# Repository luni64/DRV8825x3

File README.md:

# DRV8825x3
Carrier for 3 DRV8825 Stepper drivers

[Board and Schematic (pdf)](https://github.com/luni64/DRV8825x3/raw/master/media/)

### See also here https://github.com/luni64/mmStep for a [SparkFun MicroMode](https://www.sparkfun.com/micromod) compatible carrier for 4 DRV8825 boards.

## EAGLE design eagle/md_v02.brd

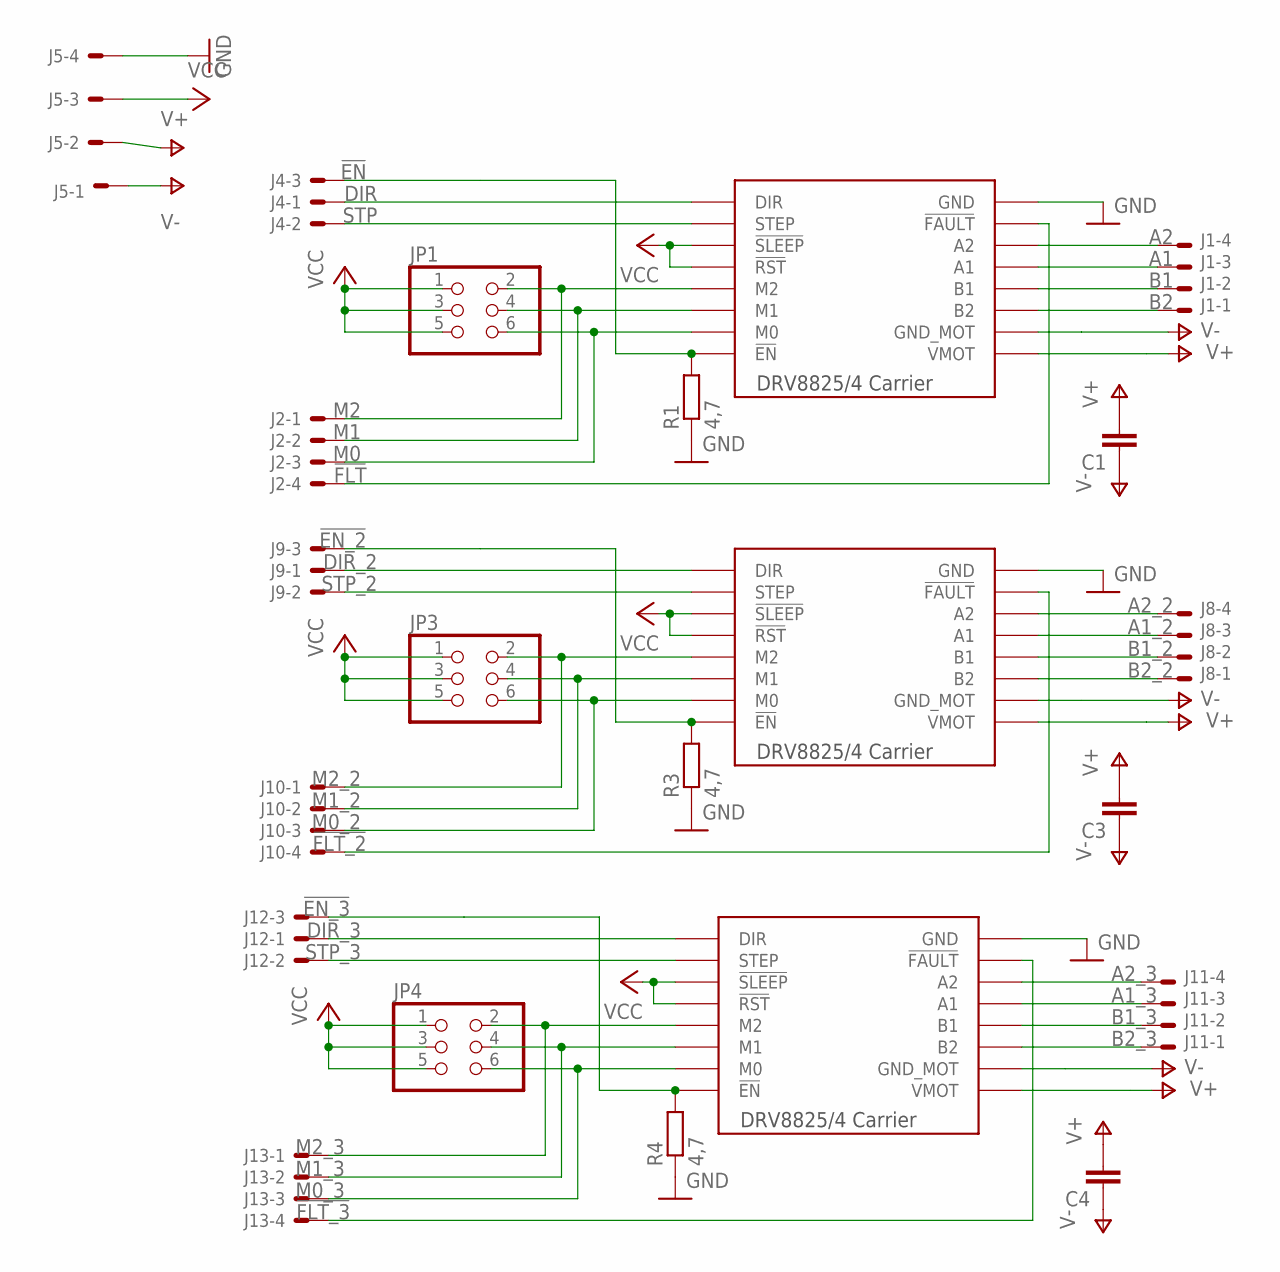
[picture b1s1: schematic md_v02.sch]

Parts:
C1, C3, C4: C-EU050-035X075; C050-035X075
J1, J2, J5, J8, J10, J11, J13: 22-27-2041-04; 6410-04
J4, J9, J12: 22-27-2031-03; 6410-03
JP1, JP3, JP4: PINHD-2X3; 2X03
M1, M3, M4: DRV8825_CARRIER"; DRV882_CARRIER
R1, R3, R4: 4,7; 0204/7

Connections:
!EN: J4.3, M1.EN (!EN), R1.2
!EN_2: J9.3, M3.EN (!EN), R3.2
!EN_3: J12.3, M4.EN (!EN), R4.2
!FLT: J2.4, M1.!FLT (!FAULT)
!FLT_2: J10.4, M3.!FLT (!FAULT)
!FLT_3: J13.4, M4.!FLT (!FAULT)
A1: J1.3, M1.A1
A1_2: J8.3, M3.A1
A1_3: J11.3, M4.A1
A2: J1.4, M1.A2
A2_2: J8.4, M3.A2
A2_3: J11.4, M4.A2
B1: J1.2, M1.B1
B1_2: J8.2, M3.B1
B1_3: J11.2, M4.B1
B2: J1.1, M1.B2
B2_2: J8.1, M3.B2
B2_3: J11.1, M4.B2
DIR: J4.1, M1.DIR
DIR_2: J9.1, M3.DIR
DIR_3: J12.1, M4.DIR
GND: J5.4, M1.GND, M3.GND, M4.GND, R1.1, R3.1, R4.1
M0: J2.3, JP1.6, M1.M0
M0_2: J10.3, JP3.6, M3.M0
M0_3: J13.3, JP4.6, M4.M0
M1: J2.2, JP1.4, M1.M1
M1_2: J10.2, JP3.4, M3.M1
M1_3: J13.2, JP4.4, M4.M1
M2: J2.1, JP1.2, M1.M2
M2_2: J10.1, JP3.2, M3.M2
M2_3: J13.1, JP4.2, M4.M2
STP: J4.2, M1.STEP
STP_2: J9.2, M3.STEP
STP_3: J12.2, M4.STEP
V+: C1.2, C3.2, C4.2, J5.2, M1.VMOT, M3.VMOT, M4.VMOT
V-: C1.1, C3.1, C4.1, J5.1, M1.GND_MOT, M3.GND_MOT, M4.GND_MOT
VCC: J5.3, JP1.1, JP1.3, JP1.5, JP3.1, JP3.3, JP3.5, JP4.1, JP4.3, JP4.5, M1.RST (!RST), M1.SLP (!SLEEP), M3.RST (!RST), M3.SLP (!SLEEP), M4.RST (!RST), M4.SLP (!SLEEP)

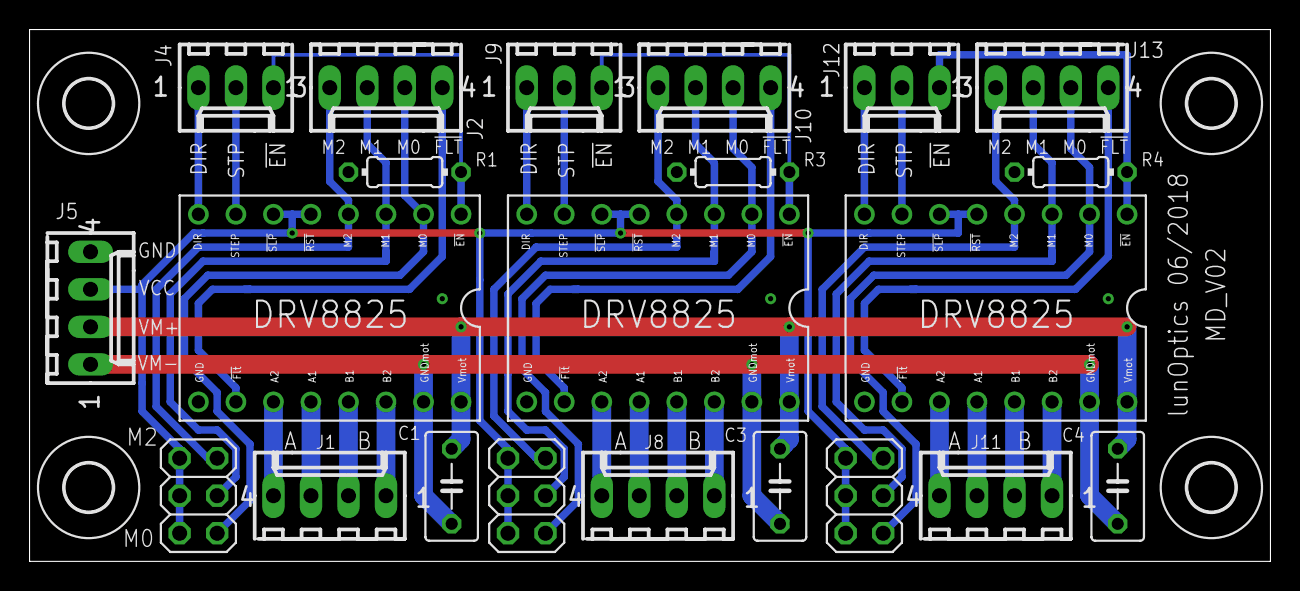
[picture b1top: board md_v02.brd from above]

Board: 2 copper layers, 84.0 x 36.0 mm, 26 parts (0 on the bottom side), 37 nets.

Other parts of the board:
U$1, U$2, U$3, U$4: 3,2

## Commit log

2019-01-28 readme
2019-01-28 Create LICENSE
2020-12-27 Added link to mmStep
